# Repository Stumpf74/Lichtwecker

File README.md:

<h1>Lichtwecker mit Touchdisplay und ESP32</h1>
Auf der Suche nach dem passenden Lichtwecker, bin ich der Meinung das es nichts gutes auf dem Markt gibt. Darum selber machen!
Es ist noch nicht perfekt aber aufgrund der begrenzten Zeit erstmal gut genug für mich.
Das ganze ist Opensource und damit viel Spaß damit!

<br />
<br />
<div align="center">
   
</div>
<br />

## Features Version 1
-   WIFI
    -   NTP-Zeitabgleich mit Sommerzeitumstellung
    -   Webserver für Weckeinstellungen, Statusanzeige, Lichtfunkiton und Einstellung der Radiostream Quellen 

-   MQTT
    -   Status und Logausgabe
    -   Einstellen der Weckfunktionen

-   Touchdisplay
    -   Anzeige der Uhrzeit und Datum
    -   Menüführung Wecker, Radiostream, Licht und Statusinfo   

-   Audiostream
    -   I2S 3W Audiokonverter für Webradio

-   RGB LED-Streifenansterung WS2812B
    -   Für den Sonnenaufgang 30 Minuten vor Weckzeit

Als Herzstück setze ich den ESP32 D1 Mini ein, der alle Arbeit übernimmt.
Dazu ein 3,5" TFT Touchdisplay mit 320x480 Punkten. Für die Audioausgabe ein Modul von Adafruit "I2S 3W Class D Amplifier - MAX98357A" das man zu hauf beim großen "A" finden kann. Ich wollte das Ganze ziemlich einfach halten um nicht an der Komplexität die auch kleine Projekte haben können zu scheitern. Den Lautsprecher habe ich aus altem Spielzeug der Kinder ausgebaut. Und damit gings dann los!

## Schaltplan
<br />
<br />
<div align="center">
   
</div>
<br />

Auch am Schaltplan kann man sehen das ich alles sehr einfach gehalten habe. Das einzige was ich mir als Elektroniker nicht verbeißen konnte ist ein 1000F Kondensator, der die Leistung aus der USB-Schnittstelle unterstützen soll. Alles andere ist sehr schlicht und fliegend verdrahtet.  

Als Spannungsversorgung habe ich eine USB-C Buchse verbaut. Ich bnutze an dieser Buchse nur die 5V Spannnungsversorgung und missbrauche die Weiße Leitung für die Ansteuerung des LED Streifens. Damit kann ich mit einem USB Kabel den Wecker mit Strom versorgen aber auch den LED-Streifen ansteuern ohne ein weiteres Kabel zu benötigen. Damit macht es den WAF (woman acceptance factor) um einiges besser. 

## Software
Ich habe das Projekt in Visual Studio Code mit Platform IO aufgesetzt, da es gut mit den Arduino LIB zusammen arbeitet. 

#Verwendete LIBS
-   AduinoJsoon
-   AsyncTCP
-   ESP32-audioI2S
-   ESPAsyncWebServer
-   PubSubClient
-   Ringbuffer
-   SolarCalculator
-   TFT_eSPI

Das Ziel bei der Software war es übersichtlich zu bleiben. Alleine Anhand der verwendeten Libs sieht man das sich das Projekt dann doch etwas erweitert hat.
Json wird für MQTT und auch für den Datenaustausch zwischen Webservice und Applikation verwendet. Auch das speichern der Daten im interen LittleFS verwendet Json.
Die Daten werden persistent im Flash gespeichert um bei einem Neustart nicht wieder eingegen werden zu müssen. 
Das gilt auch für die gespeicherten Radiostrem Adressen. Der RIngbuffer macht es einfacher die Daten ohne eine möglichen Speicherüberlauf zu verwalten.
Den SolarCalculator benötige ich für Sommer und Winter. Im Sommer benötige ich keine Sonnenaufgang, da ich keine Roladen im Zimmer habe. Anhand dees Sonnenaufgangs bleibt diese Funktion dann aus.
Am Schluss noch TFT_eSPI. Ich wollte einfach nicht die ganze TFT Ansteuerung selbst schreiben, das war mir doch zuviel.

Wie man damit schon erkennen kann, war das Projekt nun doch etwas umfangreicher als gedacht. 
Ich habe lange mit der Speicherverwaltung gekämpft, da der Audiostream nicht vernachlässigt werden will und das RAM doch sehr begrenzt ist. Auch heute gibt es beim Radio hören und gleichzeitigen Einstellen der Weckzeiten per Website Probleme. Aber das mache ich dann halt nicht zur gleichen Zeit.

Dann viel Spaß damit.
Über Rückmeldungen würde ich mich freuen!

<!-- 

<div align="center">
    
    <div>DroneBridge for ESP32 can be used to control drone swarms at a low cost.</div>
</div>
<br />
<div>
DroneBridge for ESP32 supports ESP-NOW LR, enabling ranges of more than 1km with external receiving antennas.<br />The number of drones is only limited by the channel capacity and the ESP32s processing power. All data is encrypted using AES256-GCM.
</div>

## Drone Light Show Edition (DLSE)

Special version that is optimised to work for Drone Shows using [Skybrush](https://skybrush.io/)    
Check [drone-bridge.com](https://drone-bridge.com) to get the latest release!

-   Support for Skybrush
-   Remote Power Management (sleep, wakeup) of the show drone
-   Lots of additional checks to improve safety and reliability
-   [Open Source Commercial Support Suite](https://github.com/DroneBridge/DLSECommercialSupportSuite) to help you flash, manage & maintain your drones efficiently. Script your own tools following the given examples using the DLSE API.
-   Over The Air (OTA) Updates for the ESP32
-   WiFi6 (OFDMA) & 5GHz support on supported ESP32 chips
-   ESP32-C3, ESP32-C5 & ESP32-C6

## Hardware

**Officially supported and tested boards:**  
Do the project and yourself a favour and use one of the officially supported and tested boards below.   
These boards are very affordable, have everything you need, and are also very compact. Perfect for use on any drone. 

**[You can find more info on how to get the official boards here!](https://dronebridge.gitbook.io/docs/dronebridge-for-esp32/hardware-and-wiring#officially-supported-boards)**

[For further info please check the wiki!](https://dronebridge.gitbook.io/docs/dronebridge-for-esp32/hardware-and-wiring)

## Installation/Flashing using precompiled binaries

[It is recommended that you use the official online flashing tool!](https://drone-bridge.com/flasher/)

In any other case, there are multiple ways how to flash the firmware.  
**[For further info please check the wiki!](https://dronebridge.gitbook.io/docs/dronebridge-for-esp32/installation)**

## Wiring

1.  Connect the UART of the ESP32 to a 3.3V UART of your flight controller. It is not recommended to use the ESP32s pins that are marked with TX & RX since they often are connected to the internal serial ouput. Go for any other pin instead!
2.  Set the flight controller port to the desired protocol.

**Check out the manufacturer datasheet! Only some modules can take more than 3.3V. Follow the recommendations by the ESP32 board manufacturer for powering the device**  
**[For further info please check the wiki!](https://dronebridge.gitbook.io/docs/dronebridge-for-esp32/hardware-and-wiring)**

## Configuration
1.  Connect to the WiFi `DroneBridge ESP32` with password `dronebridge`
2.  In your browser type: `dronebridge.local` (Chrome: `http://dronebridge.local`) or `192.168.2.1` into the address bar.
 **You might need to disable the cellular connection to force the browser to use the WiFi connection**
3.  Configure as you please and hit `save`

**[For further info please check the wiki!](https://dronebridge.gitbook.io/docs/dronebridge-for-esp32/configuration)**

## Use with QGroundControl, Mission Planner or any other GCS

-   The ESP will auto-send data to all connected devices via UDP to port 14550. QGroundControl should auto-connect using UDP
-   Connect via **TCP on port 5760** or **UDP on port 14550** to the ESP32 to send & receive data with a GCS of your choice. 
-   **In case of a UDP connection the GCS must send at least one packet (e.g. MAVLink heart beat etc.) to the UDP port of the ESP32 to register as an endpoint. Add ESP32 as an UDP target in the GCS**
-   Manually add a UDP target using the web interface

## Further Support

For questions or general chatting regarding DroneBridge for ESP32 please visit the Discord channel  
<div>

</div>

[contributors-shield]: https://img.shields.io/github/contributors/DroneBridge/ESP32.svg?style=for-the-badge
[contributors-url]: https://github.com/DroneBridge/ESP32/graphs/contributors
[forks-shield]: https://img.shields.io/github/forks/DroneBridge/ESP32.svg?style=for-the-badge
[forks-url]: https://github.com/DroneBridge/ESP32/network/members
[stars-shield]: https://img.shields.io/github/stars/DroneBridge/ESP32.svg?style=for-the-badge
[stars-url]: https://github.com/DroneBridge/ESP32/stargazers
[issues-shield]: https://img.shields.io/github/issues/DroneBridge/ESP32.svg?style=for-the-badge
[issues-url]: https://github.com/DroneBridge/ESP32/issues -->

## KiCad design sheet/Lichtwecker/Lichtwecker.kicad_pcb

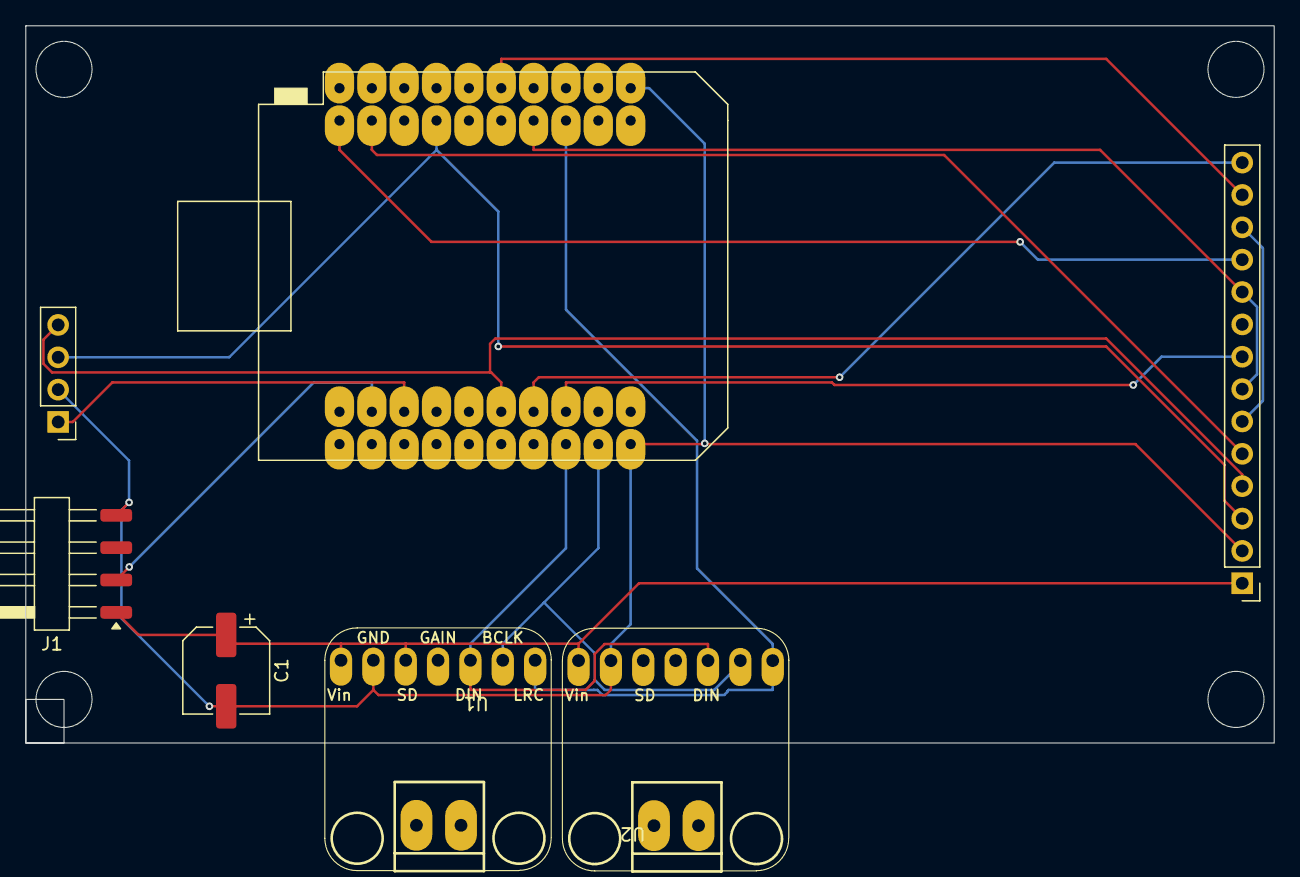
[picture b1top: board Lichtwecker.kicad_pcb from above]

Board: 2 copper layers, 98.0 x 56.3 mm, 6 parts (0 on the bottom side), 15 nets.

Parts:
C1: 1000uF; CP_Elec_6.3x5.9
J1: Conn_01x04_Pin; Harwin_M20-89004xx_1x04_P2.54mm_Horizontal
MOD1: esp32-wemos-d1-mini
U1, U2: adafruit-MAX98357
U3: 3.5_TFT_Touch_SPI_Display

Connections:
+5V: C1.1, J1.1, MOD1.35 (VCC_(USB)), U1.1 (Vin), U1.3 (~SD_MODE), U2.1 (Vin), U3.1 (VCC)
GND: C1.2, J1.4, MOD1.1 (GND), MOD1.22 (GND), U1.2 (GND), U2.2 (GND), U3.2 (GND)
unnamed: MOD1.14 (IO_05/D8), U3.3 (TFT_CS)
unnamed: MOD1.20 (IO_10/SD3), U3.11 (TP_CS)
unnamed: MOD1.18 (IO_13/TCK), U3.5 (TFT_DC_RS)
unnamed: MOD1.29 (IO_17/D3), U3.4 (TFT_RESET)
unnamed: MOD1.8 (IO_18/D5), U3.7 (TFT_SCK), U3.10 (TP_CLK)
unnamed: MOD1.27 (IO_21/D2/SDA), U3.14 (TP_IRQ)
unnamed: MOD1.25 (IO_22/D1/SCL), U3.8 (LED)
unnamed: MOD1.26 (IO_25), U1.5 (DIN), U2.5 (DIN)
unnamed: MOD1.6 (IO_26/D0), U1.7 (LRC), U2.7 (LRC)
unnamed: MOD1.24 (IO_27), U1.6 (BCLK), U2.6 (BCLK)
unnamed: MOD1.9 (IO_33), U3.13 (TP_OUT)
unnamed: MOD1.11 (IO_34), U3.6 (TFT_SDI), U3.12 (TP_DIN)
RGB_SDA: J1.2, MOD1.37 (TD0)

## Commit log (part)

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2020-01-11 Lichtwecker initial
2020-01-19 ADD: Lichtwecker: Set NTP data for time event, profile for the sunrise added
2020-01-26 ADD: Lichtwecker: Funktion zum überprüfen der Alarmzeit eingebaut.
2020-02-07 ADD: Teichsteuerung: Arbeitsstand
2020-02-10 ADD: Datensammlung: Webradio Projekt als Beispiel
2020-09-18 OPT: Set to ESP8266 and cTime from std
2020-09-21 ADD: Set RGB Function added
2020-09-21 OPT: Add configuration for windows
2020-09-21 ERR: Remove "Luefter" in config file
2020-09-21 ERR. Bugfix for the correct pinning
2020-09-21 OPT: only for transfer
2020-09-23 ADD: MQTT msg handler for android mqtt alarm clock added "before"
2020-09-23 OPT: sunrise gradient changed
2020-09-23 ADD: Auto switch leds off after 15 min
2021-01-07 OPT: Bugfix
2021-02-18 OPT: BME280 added for pressure and temp
2021-02-18 OPT: Initial AVG Value added
2021-09-22 OPT: Modify time loops an set the Version to 1.0
2021-09-22 OPT: Remove old data
2022-01-19 ADD: Datasheet for BME280 added
2022-01-19 OPT: New Log class. Set MQTT Target to Lichtwecker_Max
2022-01-19 ERR: Set String in MQTT callback. Add Datasheet for ESP32
2022-01-25 ADD: Simulation for ligth show added
2022-02-01 ADD: Touchsensor switch added
2022-02-01 ERR: recursiv call of Publish funktion
2022-02-02 OPT: preprocessor derectives for Teich, Max, Amelie and Lichtwecker
2022-02-23 OPT: Some smal changes
2022-11-24 OPT: Bugfix for the Touch senor
2023-09-28 OPT: Changes for the build with the old Lichtwecker with 8266
2026-01-06 ADD: Neu Version mit SPI-Display und neue Dateistruktur
2026-01-06 OPT: Readme angepasst
2026-01-06 Update README with current project status and components
2026-01-07 OPT: Dateileichen entfernt und Secrets.h eingeführt
2026-01-07 OPT: Nicht benötigte Dateien entfernt
2026-01-07 OPT: Weitere Werte ausgelagert
